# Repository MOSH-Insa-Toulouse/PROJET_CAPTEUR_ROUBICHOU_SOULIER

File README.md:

# Projet Capteur Graphite ROUBICHOU SOULIER
Bienvenue sur notre Github, découvrez notre travail !

# Sommaire
<!-- TOC depthFrom:2 -->
  - [1. Description](#1-description)
  - [2. Arduino](#2-arduino)
     - [2.1. Bibliothèques](#22-bibliothèques)
     - [2.2. Notre code Arduino](#22-notre-code-arduino)
  - [3. KICAD](#3-kicad)
  - [4. Application Android](#4-application-android)
     - [4.1. MIT App Inventor](#41-mit-app-inventor)
     - [4.2. Installer une application](#42-installer-une-application)
     - [4.3. Notre application](#43-notre-application)
  - [5. Bancs de test](#5-bancs-de-test)
     - [5.1. Première version](#51-première-version)
     - [5.2. Seconde version](#52-seconde-version)
     - [5.3. Résultats](#53-résultats)
  - [6. Améliorations possibles](#6-améliorations-possibles)
  - [7. Informations sur les auteurs](#7-informations-sur-les-auteurs)
<!-- /TOC -->

## 1. Description

Ce Git contient toutes les ressources nécessaires pour le projet capteur 2021 du Génie Physique de l'INSA de Toulouse. Ce projet à pour but le développement d'un **capteur de déformation** à bas coût et écoresponsable. Notre capteur exploite la dépendance entre la conductivité électrique et l’espace moyen entre les particules au sein d’un système granuleux. Le transport des électrons entre les nanoparticules de graphite est régi par l’effet tunnel. Ainsi, l’extension et la contraction du réseau percolé induit par un stress mécanique affectent la distance inter-particule et donc la conductivité électrique globale de la couche de graphite. L’écriture au crayon sur du papier permet la mise en place d’une couche de graphite présentant un réseau percolé. Sa déformation provoque une variation de résistance réversible et exploitable pour créer un extensomètre. Le conditionneur de notre capteur est un Shield comportant un circuit transimpédence ainsi que des interfaces pour un module bluetooth, une roue codeuse et un écran OLED. Ce dernier à été réalisé sur **KICAD**. Le code principal à été réalisé en C++ sur l'**IDE Arduino**. Un application téléphone à été développée sur **MIT App Inventor** pour communiquer et recevoir des données à distance, mais aussi pour contrôler les paramètres du capteur. Un banc de mesure réalisé en **impression 3D** nous permet à l'aide d'un servomoteur d'étudier la réponse en déformation de différents capteurs (dont la concentration en graphite varie).

**Code Arduino**

- Mesure la tension de sortie du circuit transimpédance
- Envoie la mesure de la tension en Bluetooth sur 1 octet
- Calcule la résistance du capteur de graphite connaissant la fonction de transfert du conditionneur
- Affiche les mesures de tension, de résistance et la fréquence d'acquisition choisie sur un écran oled 128x64
- Gère l'encodeur rotatoire pour changer la fréquence d'acquisition

**KICAD**

- PCB sous forme de Shield pour carte Arduino UNO
- Interface du capteur graphite via un circuit transimpédance
- Interface un module Bluetooth
- Interface un écran oled
- Interface un encodeur rotatoire

**Application**

- Récupère la mesure de tension
- Calcule la résistance du capteur de graphite connaissant la fonction de transfert du conditionneur
- Affiche la valeur de la résistance en MΩ
- Trace un graphique qui décrit l'évolution de la mesure de tension au cours du temps
- Mise à l'échelle automatique de l'ordonnée du graphique
- Possibilité de changer la fréquence d'acquisition (100 ou 20 Hz)
- Possibilité de mettre sur ON ou OFF l'application en temps réel

**Banc de test**

- Fonctionne avec un servomoteur
- Permet de générer des contraintes avec des consignes d'angles
- Permet une grande plage de contraintes
- Améliore la répétabilité des mesures
- Permet la mise en place de mesures autonomes
- Limite la déterioration des capteurs de graphite

## 2. Arduino

_Comment installer l'IDE Arduino sur sa machine? Vous trouverez la réponse [ici](https://www.arduino.cc/en/software)_

### 2.1 Bibliothèques

- Installez la bibliothèque "Adafruit GFX Library" [ici](https://github.com/adafruit/Adafruit-GFX-Library)
- Installez la bibliothèque "Adafruit SSD1306" [ici](https://github.com/adafruit/Adafruit_SSD1306)
- Installez la bibliothèque "Adafruit BusIOa" [ici](https://github.com/adafruit/Adafruit_BusIO)

_Comment installer une bibliothèque Arduino? Vous trouverez la réponse [ici](https://www.arduino.cc/en/Guide/Libraries#how-to-install-a-library)_

### 2.2. Notre code Arduino

Le code que nous avons développé permet de:
- Mesurer la tension de sortie du circuit transimpédance
- Envoyer la mesure de la tension en Bluetooth sur 1 octet
- Calculer la résistance du capteur de graphite connaissant la fonction de transfert du conditionneur
- Afficher les mesures de tension, de résistance et la fréquence d'acquisition choisie sur un écran oled 128x64
- Gèrer l'encodeur rotatoire pour changer la fréquence d'acquisition

**Notre code Arduino est à télécharger [ici](https://github.com/MOSH-Insa-Toulouse/PROJET_CAPTEUR_ROUBICHOU_SOULIER/blob/230c8323b89008d6615a6afa0b6356e3ce4d4a17/Code%20Arduino/Projet_Capteur.ino)** 

``` c++
#include <SoftwareSerial.h>
#include <Arduino.h>
#include <SPI.h>
#include <Wire.h>
#include <Adafruit_GFX.h>
#include <Adafruit_SSD1306.h>
double sensorValue;
double sensorVolt;

/////////////////OLED//////////////////////////////////////
#define OLED_RESET 4
Adafruit_SSD1306 display(-1);

#define NUMFLAKES 10
#define XPOS 0
#define YPOS 1
#define DELTAY 2
#define LOGO16_GLCD_HEIGHT 32
#define LOGO16_GLCD_WIDTH  128 

///////////////////Bluetooth////////////////////////////////
#define rxPin 10
#define txPin 11
#define baudrate 9600
#define pin A0
int etat;
SoftwareSerial mySerial(rxPin,txPin);
String c = "b";

//////////////////////ROUE//////////////////////////////////
#define encoder0pinA 2
#define encoder0pinB 4
#define Switch 5
volatile unsigned int freq = 50;

/////////////////////FCT ECRAN/////////////////////////////
void OLED(String text, int x, int y,int size, boolean d) 
{
  display.setTextSize(size);
  display.setTextColor(WHITE);
  display.setCursor(x,y);
  display.println(text);
  
  if(d)
  {
    display.display();
  }
  //delay(100);
}

////////////////////FCT ROUE//////////////////////////////
void doEncoder()
{
  if(digitalRead(encoder0pinB)==HIGH){
    freq=10;
  }
  else
  {
    freq=50;
  }
}

void setup() 
{
///////////////Bluetooth////////////////////////////////
Serial.begin(baudrate);
pinMode(rxPin,INPUT);
pinMode(txPin,OUTPUT);
  
pinMode(pin,INPUT);
mySerial.begin(baudrate); //bluetooth

///////////////OLED/////////////////////////////////////
display.begin(SSD1306_SWITCHCAPVCC, 0x3C);//Inititalisation de l'écran
display.display();
delay(2000);
display.clearDisplay(); 

//////////////ROUE/////////////////////////////////////
pinMode(encoder0pinA,INPUT);
digitalWrite(encoder0pinA,HIGH);
pinMode(encoder0pinB,INPUT);
digitalWrite(encoder0pinB,HIGH);
attachInterrupt(0,doEncoder, RISING);//intéruption lors du mouvement de la roue
}

void loop()
{ 
/////////////////CAPTEUR//////////////////////////////  
byte val=map(analogRead(pin),0,1024,0,127);

float f=1/(freq*0.001);

int R1= 100000;
int R2 = 1000;
int R3 = 100000;
int R5 = 10000;

sensorVolt = analogRead(pin)*0.004882814; //valeur en Volt
sensorValue = (1+R3/R2)*R1*(5/sensorVolt)-R1-R5;//valeur en Mohm
//Serial.println(sensorValue);
String vString = String(sensorVolt, 2); //transforme la donnée des volt en string
String RString =  String(sensorValue, 0); //transforme la donnée de résistance en string
String fString = String(f, 3); //transforme la donnée de la fréquence en string

///////////////BLUETOOTH////////////////////////////////
if(mySerial.available()>0){
char data = mySerial.read();
String DataStr = String(data);
DataStr.trim();
Serial.println(DataStr);

if (c=!DataStr)
{
  c=DataStr;
  }

if (DataStr=="a")         ///
  {                       ///
  etat = 1;               ///
  }                       /// Mise à "ON" ou "OFF" de l'envoi des données par l'apk
else if (DataStr=="b")    ///
  {                       ///
   etat = 0;              ///
  }
else if (DataStr=="c")    ///
  {                       ///
  freq=10;                ///
  }                       ///
else if (DataStr=="d")    /// Choix de fréquence depuis l'apk
  {                       ///
  freq=50;                ///
  }                       ///
}

switch(etat)
{
  case 0:
  break;

  case 1:
  mySerial.write(val);     ///envoie la donnée à l'application
  Serial.print(val);
  break;
  }

///////////////////OLED/////////////////////////////
display.clearDisplay();
 
OLED("Res(Mohm):          ", 20, 3, 1.9, false);
OLED(RString, 90, 3, 1, false); ///Ecriture de la resistance sur l'OLED
OLED("", 110, 3, 1, false);

OLED("Volt :     ", 20, 12, 1.9, false);
OLED(vString, 80, 12, 1, false); ///Ecriture de la tension sur l'OLED
OLED("V", 110, 12, 1, false);

OLED("Freq:          ", 20, 21, 1.9, false);
OLED(fString, 72, 21, 1.9, false);  ///Ecriture de la fréquence sur l'OLED
OLED("Hz", 110, 21, 1.9, false);

display.drawRect(1, 1, 126,31, WHITE); ///Met le rectangle autour de l'oled
display.display();

delay(freq); ///Règle la fréquence d'aquisition et d'envoi
}
```

## 3. KICAD

_Comment installer KICAD sur sa machine? La réponse se trouve [ici](https://www.kicad.org/)_

Vous trouverez ci-dessous un aperçu de l'empreinte du Shield que nous avons développé. Le projet sur le logiciel KICAD permet de:

- Créer PCB sous forme de Shield pour carte Arduino UNO
- Interfacer le capteur au graphite via un circuit transimpédance
- Interfacer un module Bluetooth
- Interfacer un écran oled
- Interfacer un encodeur rotatoire

**L'empreinte au format PDF est à télécharger [ici](https://github.com/MOSH-Insa-Toulouse/PROJET_CAPTEUR_ROUBICHOU_SOULIER/tree/main/KICAD/PDF)**

**L'empreinte au format GERBER est à télécharger [ici](https://github.com/MOSH-Insa-Toulouse/PROJET_CAPTEUR_ROUBICHOU_SOULIER/tree/main/KICAD/GERBER)**

**Notre projet KICAD est à télécharger [ici](https://github.com/MOSH-Insa-Toulouse/PROJET_CAPTEUR_ROUBICHOU_SOULIER/tree/main/KICAD/Projet%20KICAD)**

Ci-dessous est l’application typique du capteur dans un circuit analogique. La résistance R5 protège l’amplificateur opérationnel des décharges électrostatiques et forme avec la capacité C1 un filtre pour les bruits en tension. La capacité C1 et la résistance R1 forment un filtre pour le bruit en courant. La résistance R2 est interchangeable pour pouvoir adapter le calibre. La capacité C4 avec la résistance R3 forment un filtre actif, tandis que C2 et R6 forment le filtre de sortie. La capacité C3 permet de filtrer le bruit sur l’alimentation. Le signal délivré par le capteur traverse un pont diviseur de tension. La tension résultante en sortie est amplifiée par l’amplificateur opérationnel LTC1050 puis elle est filtrée par un filtre RC de sortie. La tension associée à l’étiquette ADC peut être connectée à un ADC 5V. Une carte Arduino peut être utilisée à cet effet.

## 4. Application Android

### 4.1. MIT App Inventor

_Le site internet de création d'application MIT App Inventor est accessible en cliquant [ici](https://appinventor.mit.edu)_

### 4.2. Installer une application

_Comment installer un fichier .apk à partir d'un PC? La réponse se trouve [ici](https://fr.wikihow.com/installer-sur-un-Android-des-fichiers-APK-%C3%A0-partir-d%E2%80%99un-PC)_

### 4.3. Notre application

Vous trouverez ci-dessous un aperçu de l'application que nous avons développé. Cette application permet de:
- Récupérer la mesure de tension
- Calculer la résistance du capteur de graphite connaissant la fonction de transfert du conditionneur
- Afficher la valeur de la résistance en MΩ
- Tracer un graphique qui décrit l'évolution de la mesure de tension au cours du temps
- Mettre à l'échelle automatique de l'ordonnée du graphique
- Changer la fréquence d'acquisition (100 ou 20 Hz)
- Mettre sur ON ou OFF l'application en temps réel

**Le code de notre application (.aia) est à télécharger [ici](https://github.com/MOSH-Insa-Toulouse/PROJET_CAPTEUR_ROUBICHOU_SOULIER/blob/26b40920e06c2dba8526cb9ba54827a0fe55c7c3/Application/ShieldcinqA_II.aia)**

**Le code de notre application (.apk) est à télécharger [ici](https://github.com/MOSH-Insa-Toulouse/PROJET_CAPTEUR_ROUBICHOU_SOULIER/blob/f0df43999fbf93bf9aa83195ed25307b022c2bd4/Application/ShieldcinqA_II.apk)**

## 5. Bancs de test

### 5.1. Première version 

Notre première version du banc de test était une tour composée des cylindres de différents diamètres connus. Cette tour permet l'application de plusieurs contraintes à notre capteur. Cependant, ce banc conduisait à des déformations irréversibles de notre capteur. Aussi, ce banc n'était pas autonome et la reproductibilité n'était pas optimale.

### 5.2. Seconde version 

Nous sommes donc passés à un banc de test fonctionnant avec un servomoteur. Ce dernier système permet de générer des contraintes avec des consignes d'angles et autorise, de ce fait, une grande plage de contraintes. Finalement ce banc de test est optimal car il permet la mise en place de mesures autonomes, améliore la répétabilité des mesures et limite la déterioration des capteurs de graphite.

**Les fichiers STL que nous avons créés sont à télécharger au ci-dessous:**

- Banc sous forme de tour [ici](https://github.com/MOSH-Insa-Toulouse/PROJET_CAPTEUR_ROUBICHOU_SOULIER/blob/9662f01d69eacdf1dfc96737585869e709ca6d86/Bancs%20de%20test/PieceCapteur3%20v1.stl)
- Banc avec servomoteur (pièce 1) [ici](https://github.com/MOSH-Insa-Toulouse/PROJET_CAPTEUR_ROUBICHOU_SOULIER/blob/e755654e5a37c8409d6181bdfd030661f82570d9/Bancs%20de%20test/Banc1%20v3.stl)
- Banc avec servomoteur (pièce 2)[ici](https://github.com/MOSH-Insa-Toulouse/PROJET_CAPTEUR_ROUBICHOU_SOULIER/blob/b976cd1678c3cf63028d5a895135fa7c54baf83e/Bancs%20de%20test/Banc2%20v1.stl)

### 5.3. Résultats

Les caractéristiques du capteur ont été déterminées par la mesure de la résistance pour différentes déformations appliquées. L’expérience a été réalisée pour différents types de crayons (2H, HB et B) dont la concentration en graphite varie.

.png)

.png)

.png)

## 6. Améliorations possibles

- Améliorer la banc de test pour qu'il puisse faire des contrainte en extension et en contraction sur le capteur sans le retourner.
- Optimiser le type de capteur, notamment en améliroant la qualité du papier utiliser ou la façon de plastifier le capteur.
- Adapter le circuit électronique à un type de capteur pour en optimiser les performances.

## 7. Informations sur les auteurs

**Jordi ROUBICHOU & Mathias SOULIER**

- Étudiants en 4 ième année du Génie Physique de l'INSA de Toulouse

- _roubicho@etud.insa-toulouse.fr_

- _msoulier@etud.insa-toulouse.fr_

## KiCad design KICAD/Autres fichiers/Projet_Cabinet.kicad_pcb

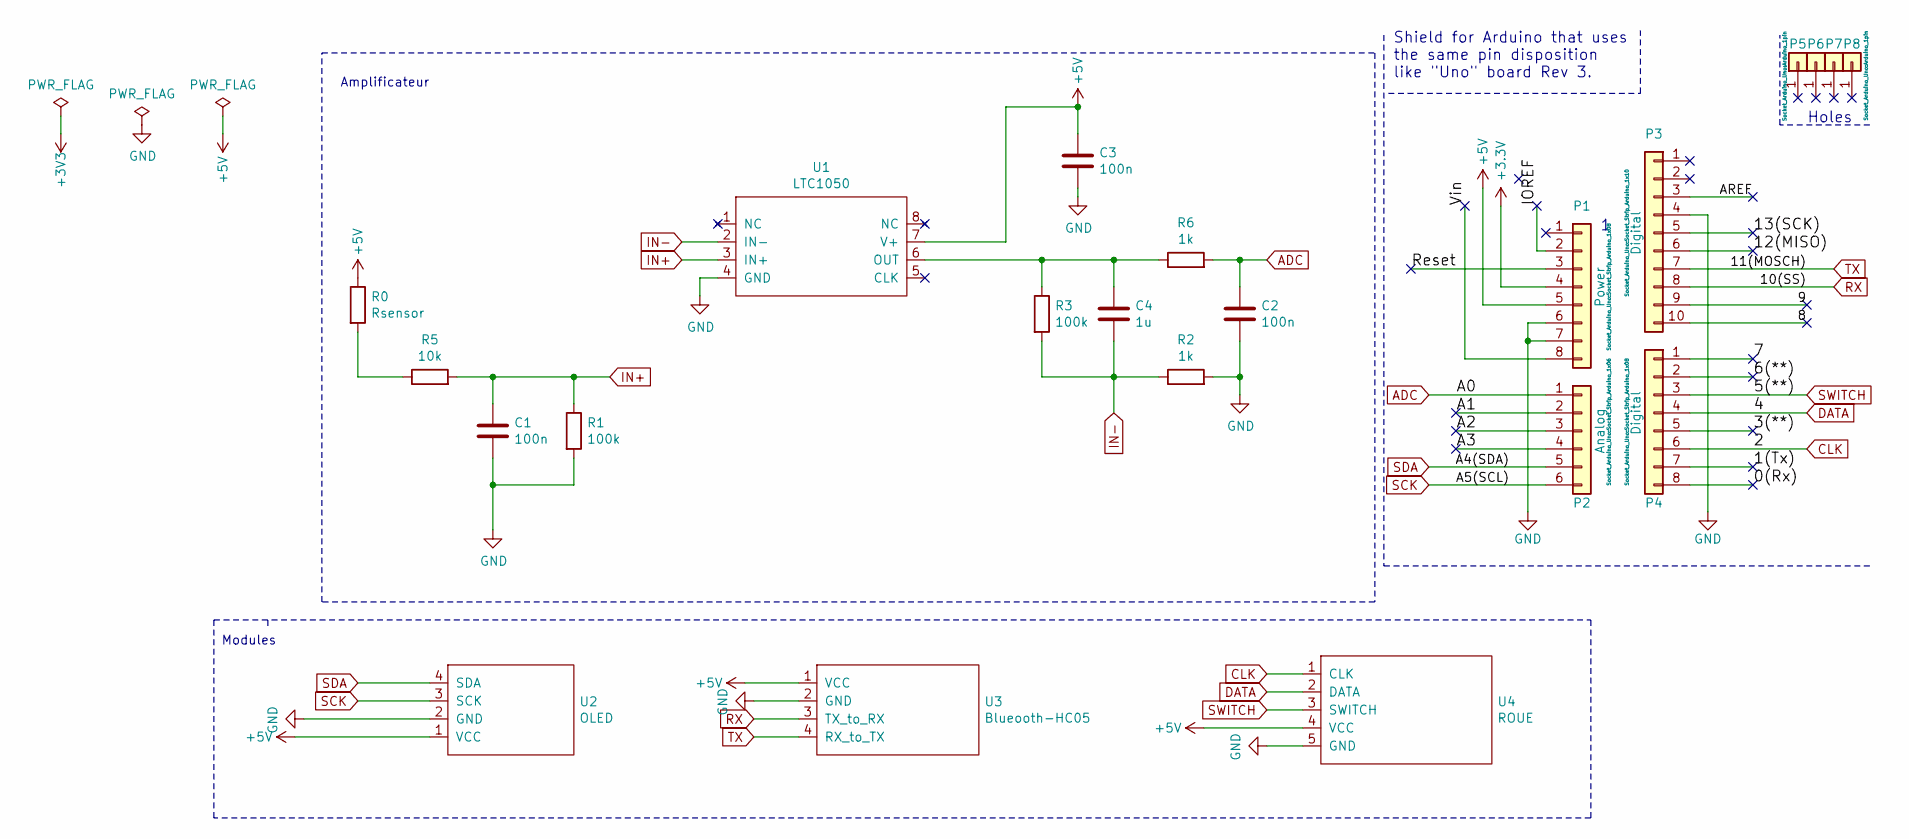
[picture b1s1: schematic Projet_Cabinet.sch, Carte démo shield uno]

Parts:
C1, C2, C3: 100n; C_Disc_D3.0mm_W1.6mm_P2.50mm
C4: 1u; C_Rect_L7.0mm_W3.5mm_P5.00mm
P1: Power; Socket_Strip_Arduino_1x08
P2: Analog; Socket_Strip_Arduino_1x06
P3: Digital; Socket_Strip_Arduino_1x10
P4: Digital; Socket_Strip_Arduino_1x08
P5, P6, P7, P8: CONN_01X01; Arduino_1pin
R0: Rsensor; R_Axial_DIN0204_L3.6mm_D1.6mm_P2.54mm_Vertical
R1, R3: 100k; R_Axial_DIN0309_L9.0mm_D3.2mm_P12.70mm_Horizontal
R2, R6: 1k; R_Axial_DIN0309_L9.0mm_D3.2mm_P12.70mm_Horizontal
R5: 10k; R_Axial_DIN0309_L9.0mm_D3.2mm_P12.70mm_Horizontal
U1: LTC1050
U2: OLED
U3: Blueooth-HC05; HC05
U4: ROUE; Roue

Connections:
+3V3: P1.4
+5V: C3.1, P1.5, R0.1, U1.7 (V+), U2.1 (VCC), U3.1 (VCC), U4.4 (VCC)
/0(Rx): P4.8
/1(Tx): P4.7
/3(**): P4.5
/6(**): P4.2
/7: P4.1
/8: P3.10
/9: P3.9
/12(MISO): P3.6
/13(SCK): P3.5
/A1: P2.2
/A2: P2.3
/A3: P2.4
/AREF: P3.3
/IOREF: P1.2
/Reset: P1.3
/Vin: P1.8
ADC: C2.1, P2.1, R6.2
CLK: P4.6, U4.1 (CLK)
DATA: P4.4, U4.2 (DATA)
GND: C1.2, C2.2, C3.2, P1.6, P1.7, P3.4, R1.2, R2.2, U1.4 (GND), U2.2 (GND), U3.2 (GND), U4.5 (GND)
IN+: C1.1, R1.1, R5.2, U1.3 (IN+)
IN-: C4.2, R2.1, R3.2, U1.2 (IN-)
unnamed: C4.1, R3.1, R6.1, U1.6 (OUT)
unnamed: R0.2, R5.1
RX: P3.8, U3.3 (TX_to_RX)
SCK: P2.6, U2.3 (SCK)
SDA: P2.5, U2.4 (SDA)
SWITCH: P4.3, U4.3 (SWITCH)
TX: P3.7, U3.4 (RX_to_TX)

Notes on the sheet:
Holes
Shield for Arduino that uses the same pin disposition like "Uno" board Rev 3.
Amplificateur
Modules

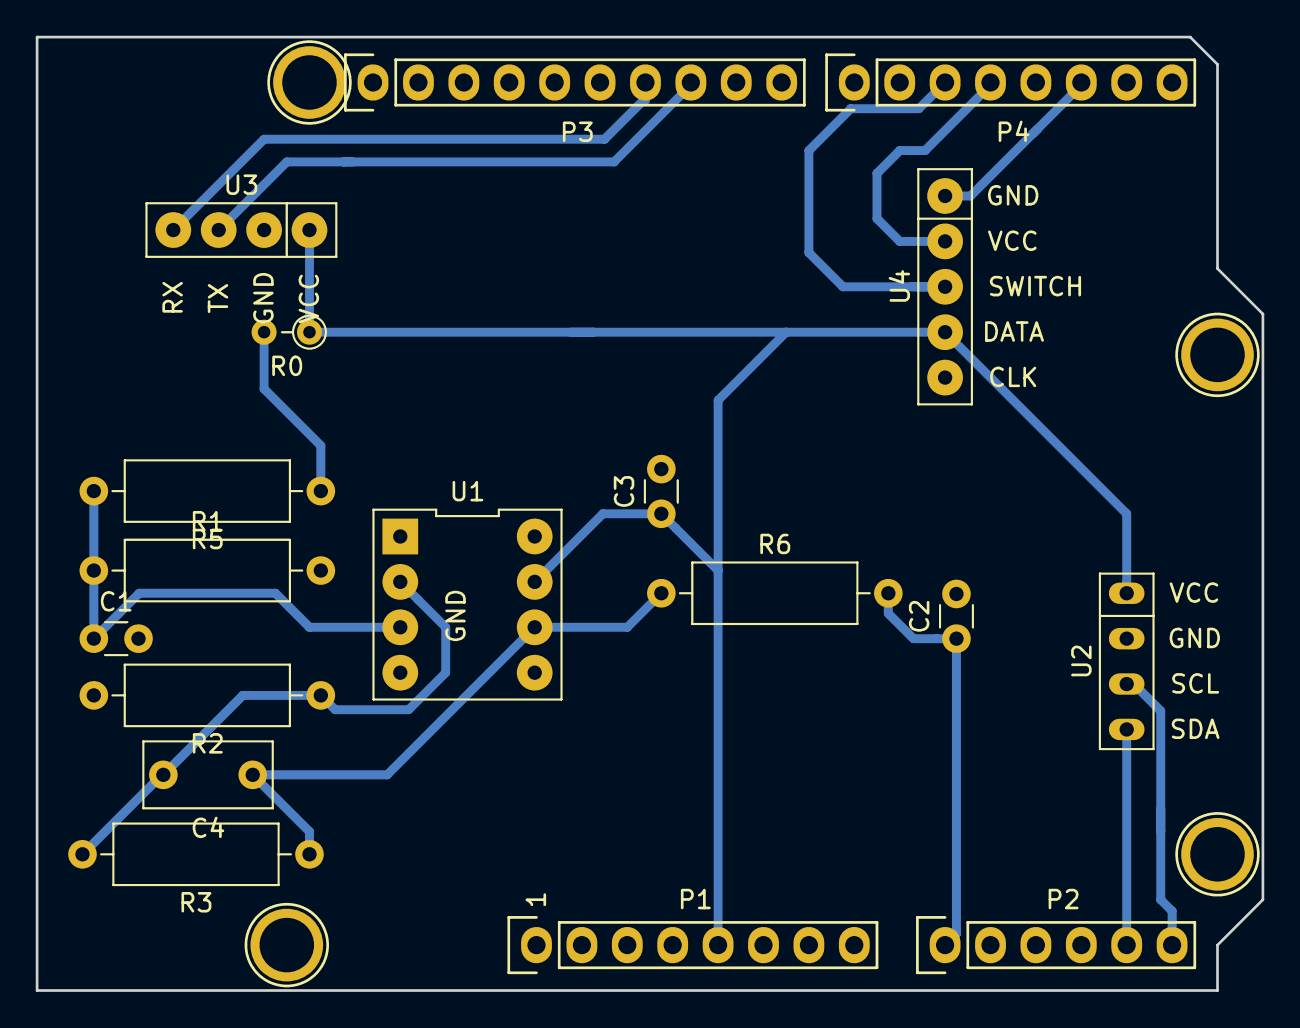
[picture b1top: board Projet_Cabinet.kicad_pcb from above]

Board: 2 copper layers, 68.6 x 53.3 mm, 22 parts (0 on the bottom side), 14 nets.

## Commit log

2021-03-26 Add files via upload
    Application
2021-03-26 Create Application android
